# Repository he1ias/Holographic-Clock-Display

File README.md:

## Holographic Display
### A 'floating' display for your bedside table

A Holographic Clock Display for your bedside table, powered by the ESP32. Using the Pepper's Ghost visual effect, this display appears to 'float' in mid-air.

Comes with a wide range of pre-programmed clock-faces, visual effects, and relaxing animations. Works best when used in a dark room.

Made for HackClub's Half Life event.

Onshape URL: [click here](https://cad.onshape.com/documents/4a07292fcf3ec5a261f2cd78/w/7a4fcc3ff990e21e98229a03/e/6ea8dd64a432b46748776d14)

### What can it do?

It can display a wide variety of clock faces & relaxing visual effects. The Pepper's Ghost 'illusion' gives the images a 3D effect. Simply connected to the ESP32 via a USB-C cable. The display comes with a builtin effect selection button and brightness knob for ease of use.

### How does it?

4 displays sit hidden inside the 3D-printed casing, pointed up at the transparent material. The material then reflects the light back at the viewer, as if the material was the source of the light itself.

### How was it made?

Using KiCad & Onshape.

I first tested the effect by cutting some acrylic:

I then selected my parts, and wired the schematic in KiCad:

I then arranged my PCB and routed my wires:

I then used online CAD program Onshape to design the 3D-printed casing for my piece. The slots hold the transparent material securely into place, and screw holes live inside the case so the PCB can be attached:

### How do I build it?

First, order the materials located in `BOM.csv` and below, 3D-print the casing (STEP and STL files are located in this repository) and print the PCB using an online service such as JLCPCB.

To assemble, solder the parts onto the PCB, screw it into place in the casing, and put the lid over the top. Cut out 4 equally sized trapeziums with `base = 3cm, top = 9cm, and height = 3√2 ~= 4.25cm`, and insert into the slots marked out.

That's it! Simply connect to the ESP32 via USB-C and the clock will turn itself on!

### Bill of Materials (BOM)

| Item | Qty | Supplier | Cost/item | Total Cost | Link |
|------|----:|----------|----------:|-----------:|------|
| XIAO RP2040 ESP32 | 1 | seeedstudio | $3.90 | $3.90 | [Link](https://www.seeedstudio.com/XIAO-RP2040-v1-0-p-5026.html) |
| Display | 4 | LCSC | $2.22 | $8.88 | [Link](https://www.lcsc.com/product-detail/C7471924.html) |
| Button | 10 | LCSC | $0.06 | $0.60 | [Link](https://www.lcsc.com/product-detail/C49393619.html) |
| Thumbwheel Potentiometer | 1 | LCSC | $1.08 | $1.08 | [Link](https://www.lcsc.com/product-detail/C470643.html) |
| Male pin headers | 5 | LCSC | $0.16 | $0.80 | [Link](https://www.lcsc.com/product-detail/C2337.html) |
| JLCPCB | 1 | JLC | $4.00 | $4.00 | [Link](https://jlcpcb.com/) |
| JLC3DP | 1 | JLC | $6.50 | $6.50 | [Link](https://www.jlc3dp.com) |
| Reflective material (eg. acrylic sheet) (Already owned) | 1 | Amazon | $0.01 | $0.01 | [Link](https://www.amazon.com.au/Pack-Clear-Acrylic-Sheets-Transparent/dp/B0H6PXC3K6) |
| M2 Screws (Already owned) | 4 | AliExpress | $0.01 | $0.04 | [Link](https://www.aliexpress.com/item/4000056753202.html) |
| Estimated total shipping | 1 | | | $13.00 | |
| **Total** | | | | **$38.81** | |

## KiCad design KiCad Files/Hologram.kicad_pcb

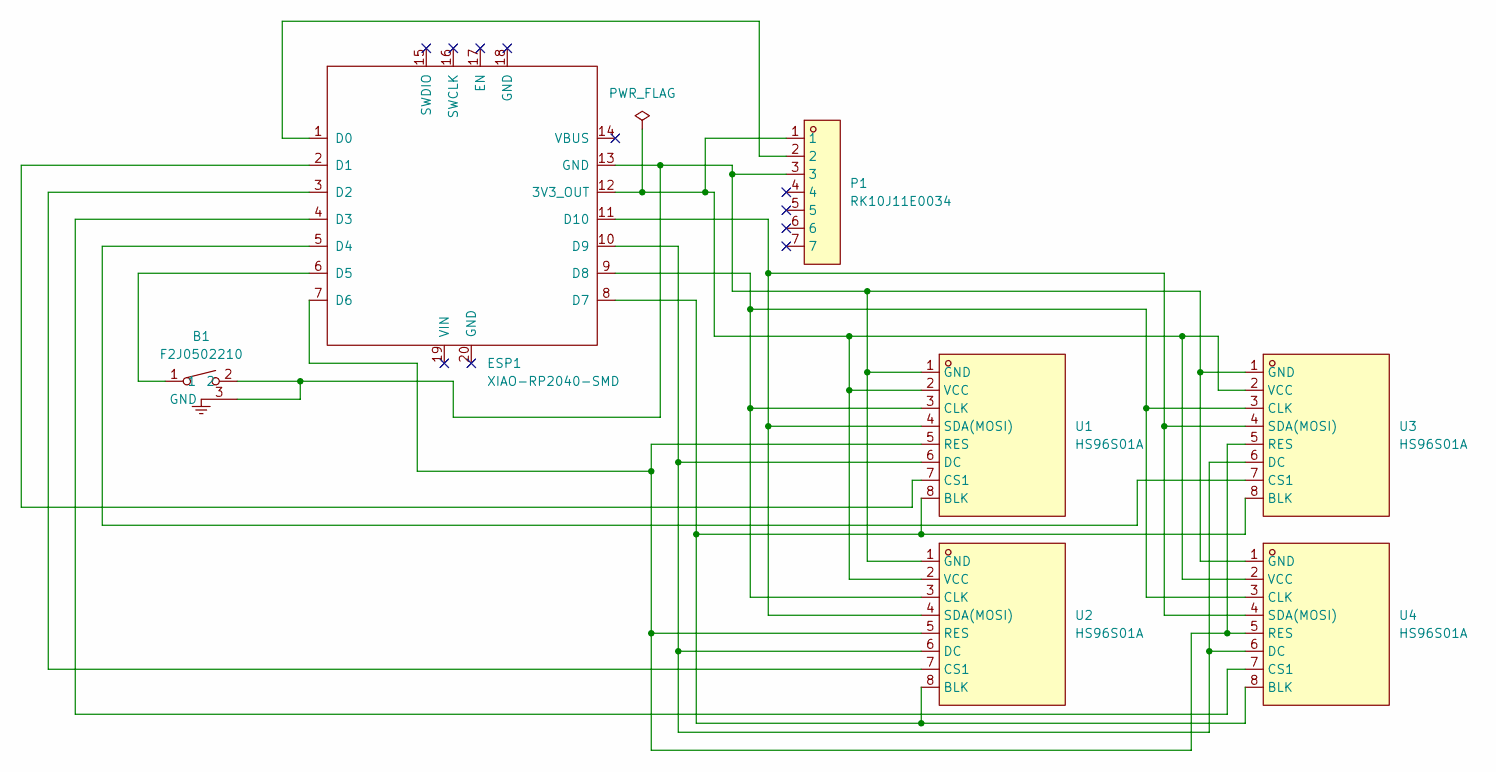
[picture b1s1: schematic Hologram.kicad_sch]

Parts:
B1: F2J0502210; SW-TH_3P-L4.5-W5.0-P3.00-LS1.9; MPN F2J0502210; LCSC Part C49393619
ESP1: XIAO-RP2040-SMD; XIAO-RP2040-DIP
P1: RK10J11E0034; RES-TH_RK10J12E0A0A; MPN RK10J11E0034; LCSC Part C470643
U1, U2, U3, U4: HS96S01A; LCD-TH_HS96S01A; MPN HS96S01A; LCSC Part C7471924

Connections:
unnamed: B1.2, B1.3 (GND), ESP1.13 (GND), P1.3, U1.1 (GND), U2.1 (GND), U3.1 (GND), U4.1 (GND)
unnamed: ESP1.12 (3V3_OUT), P1.1, U1.2 (VCC), U2.2 (VCC), U3.2 (VCC), U4.2 (VCC)
unnamed: ESP1.1 (D0), P1.2
unnamed: ESP1.2 (D1), U1.7 (CS1)
unnamed: ESP1.3 (D2), U2.7 (CS1)
unnamed: ESP1.4 (D3), U4.7 (CS1)
unnamed: ESP1.5 (D4), U3.7 (CS1)
unnamed: B1.1, ESP1.6 (D5)
unnamed: ESP1.7 (D6), U1.5 (RES), U2.5 (RES), U3.5 (RES), U4.5 (RES)
unnamed: ESP1.8 (D7), U1.8 (BLK), U2.8 (BLK), U3.8 (BLK), U4.8 (BLK)
unnamed: ESP1.9 (D8), U1.3 (CLK), U2.3 (CLK), U3.3 (CLK), U4.3 (CLK)
unnamed: ESP1.10 (D9), U1.6 (DC), U2.6 (DC), U3.6 (DC), U4.6 (DC)
unnamed: ESP1.11 (D10), U1.4 (SDA(MOSI)), U2.4 (SDA(MOSI)), U3.4 (SDA(MOSI)), U4.4 (SDA(MOSI))

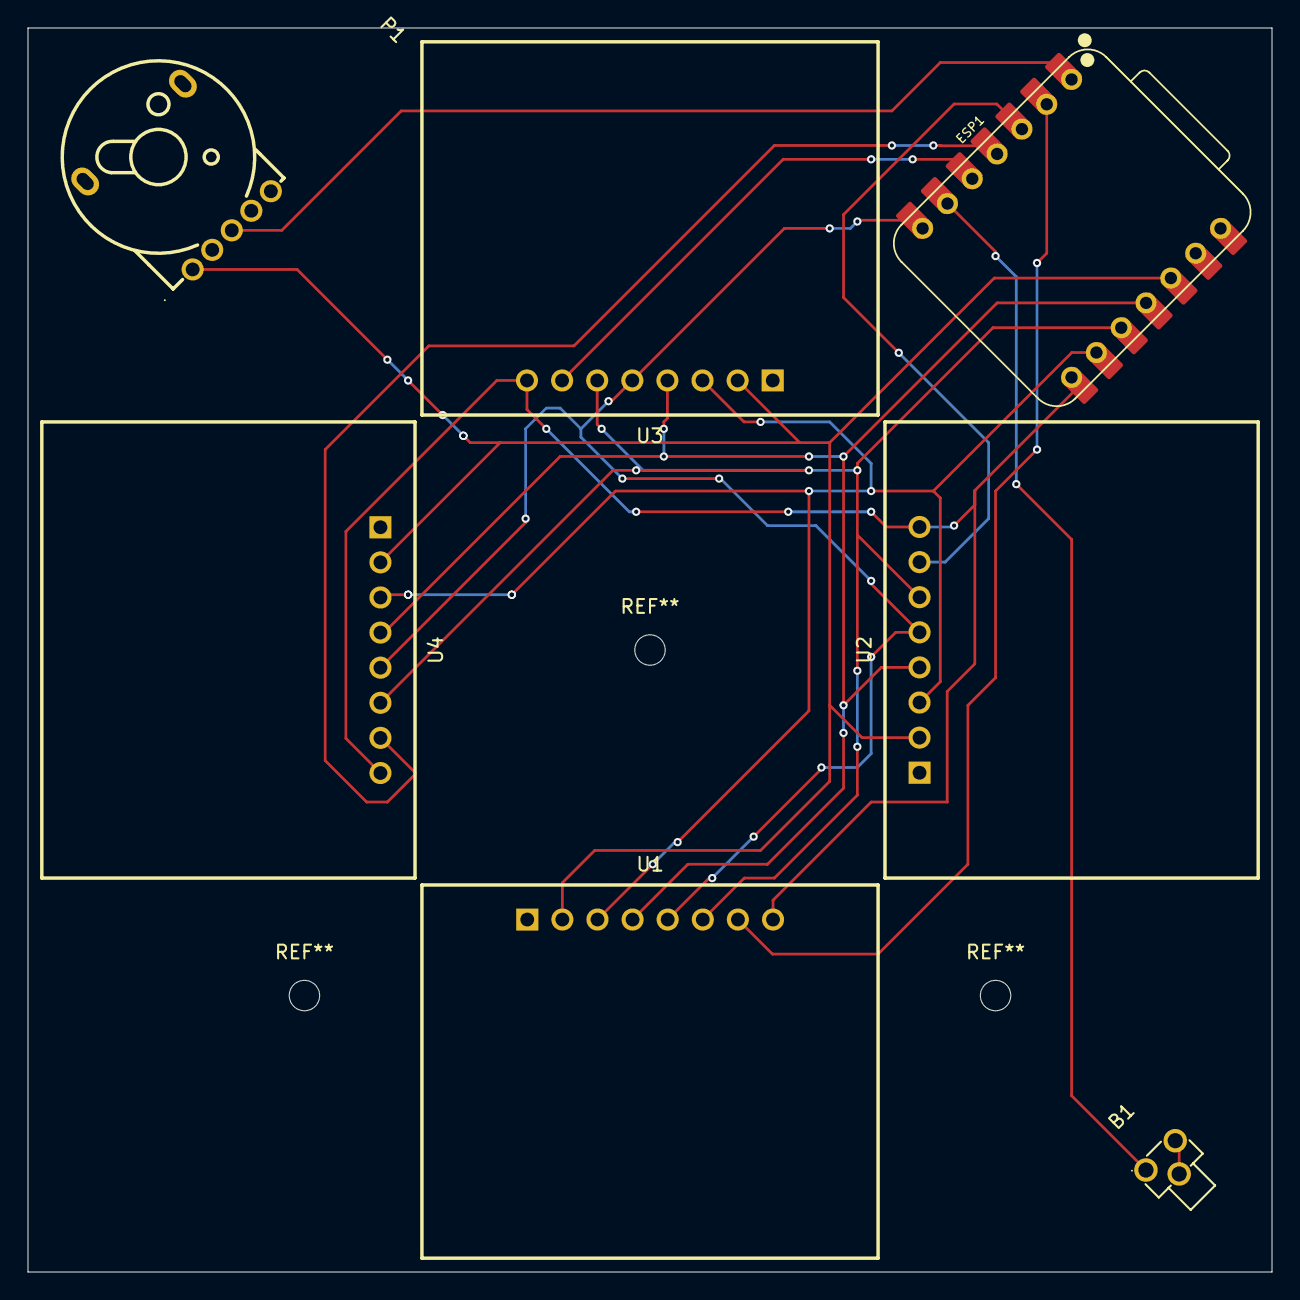
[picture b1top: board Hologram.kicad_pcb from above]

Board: 2 copper layers, 90.0 x 90.0 mm, 7 parts (0 on the bottom side), 13 nets.
